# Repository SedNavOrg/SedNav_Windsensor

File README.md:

# SedNav_Windsensor

An open-source wind sensor design, taking inspiration from the project [Windsensor Yachta](https://github.com/norbert-walter/Windsensor_Yachta) by Norbert Walter.

It uses the same firmware, modified to work with this design.

The aims of this derivation are :

- To simplify the building process, by making the PCB easier to solder by hand

- To simplify the flashing, by using the ESP32C3 or C6 with a built-in USB interface (no more need for a serial to USB converter)

- To reduce the size of the wind sensor, by shrinking the pcb and reworking the design, in order to reduce the wind resistance, making it more resilient to winds.

- To test and validate the design in an actual wind tunnel.

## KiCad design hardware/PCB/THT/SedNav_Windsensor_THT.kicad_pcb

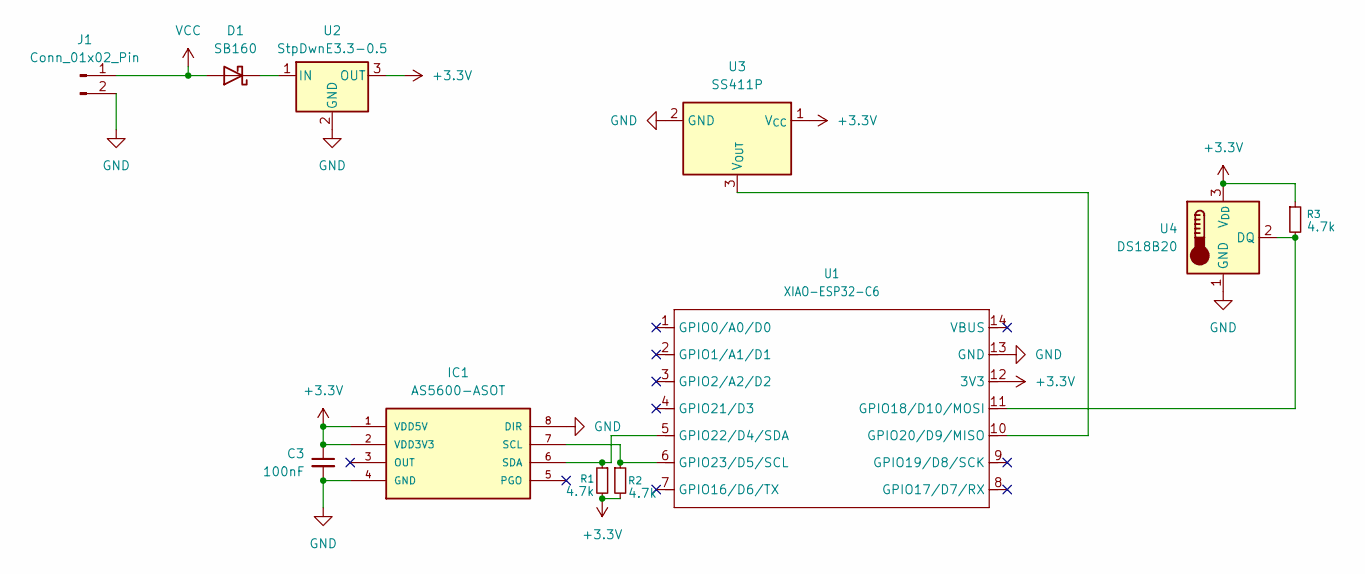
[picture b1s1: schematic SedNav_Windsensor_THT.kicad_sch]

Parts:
C3: 100nF; C_Disc_D4.7mm_W2.5mm_P5.00mm
D1: SB160; D_DO-41_SOD81_P7.62mm_Horizontal
IC1: AS5600-ASOT; SOIC127P600X175-8N; MOUSER_PART_NUMBER 985-AS5600-ASOT
J1: Conn_01x02_Pin; TerminalBlock_Phoenix_MPT-0,5-2-2.54_1x02_P2.54mm_Horizontal
R1, R2, R3: 4.7k; R_Axial_DIN0207_L6.3mm_D2.5mm_P7.62mm_Horizontal
U1: XIAO-ESP32-C6; XIAO-ESP32C6-THT
U2: StpDwnE3.3-0.5; CONV_R-78K3.3-0.5
U3: SS411P
U4: DS18B20; TO-92_Inline_Wide

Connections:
+3.3V: C3.1, IC1.1 (VDD5V), IC1.2 (VDD3V3), R1.2, R2.2, R3.1, U1.12 (3V3), U2.3 (OUT), U3.1 (V_{CC}), U4.3 (V_{DD})
GND: C3.2, IC1.4 (GND), IC1.8 (DIR), J1.2, U1.13 (GND), U2.2 (GND), U3.2 (GND), U4.1 (GND)
unnamed: D1.1 (K), U2.1 (IN)
unnamed: IC1.7 (SCL), R2.1, U1.6 (GPIO23/D5/SCL)
unnamed: IC1.6 (SDA), R1.1, U1.5 (GPIO22/D4/SDA)
unnamed: R3.2, U1.11 (GPIO18/D10/MOSI), U4.2 (DQ)
unnamed: U1.10 (GPIO20/D9/MISO), U3.3 (V_{OUT})
VCC: D1.2 (A), J1.1

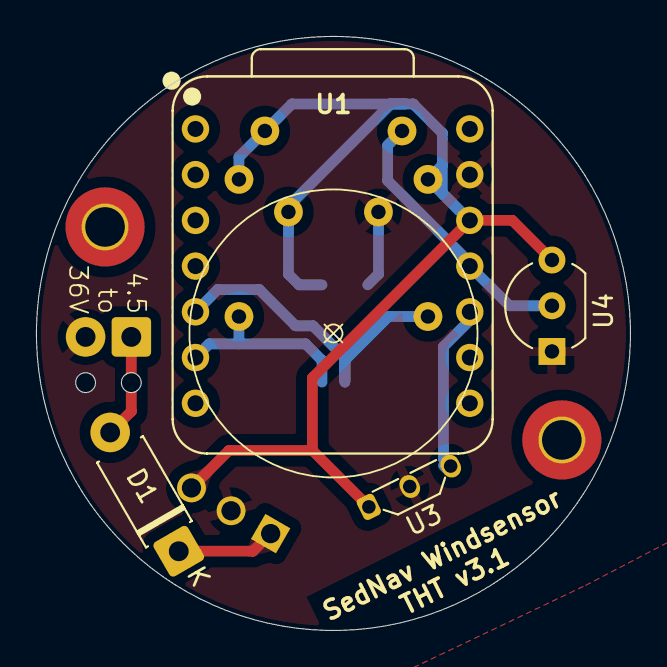
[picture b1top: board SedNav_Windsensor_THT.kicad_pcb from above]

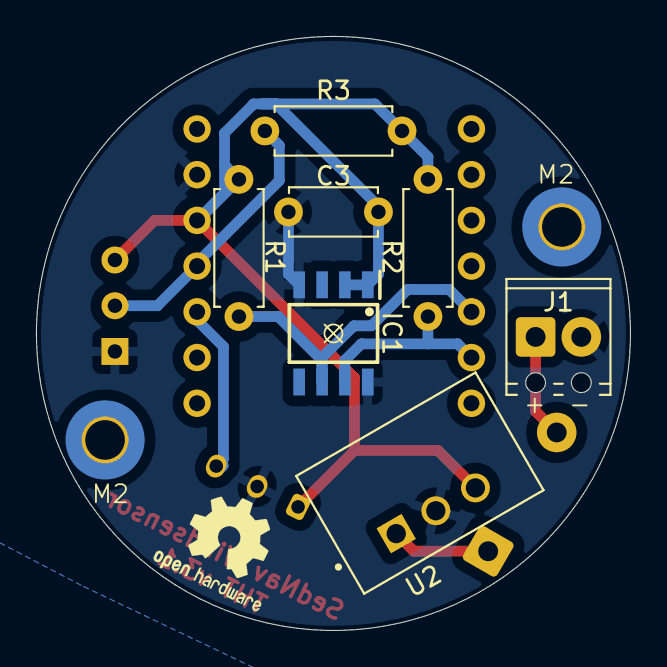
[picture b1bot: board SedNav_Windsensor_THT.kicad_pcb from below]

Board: 2 copper layers, 33.0 x 33.0 mm, 13 parts (9 on the bottom side), 8 nets.

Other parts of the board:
M2_1, M2_2: MountingHole_2.2mm_M2_Pad_TopBottom

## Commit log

2025-10-15 Corrected component sizes and added teardrops
2025-11-04 Modified PCB to match Simon's remarks Moved the esp32 to a side, to be able to access the usb port Simplified the routing Made the board more aesthetically pleasing
2025-11-15 Added software, corrected for ESP32C6 (untested)
2025-11-25 Firmware partialy operational. Need to correct the temperature, and verify the NMEA works.
2025-12-15 Corrected EEPROM initialization and saving function. Verified connecting to boat wifi works.
2025-12-16 Corrected temperature sensor bug
2025-12-17 Update README to reflect project name change and outline design aims
2025-12-19 Correction de la connexion avec hotspot non sécurisé
2025-12-21 v2 du PCB (en THT)
2026-01-22 Changed connector
2026-01-22 Version alpha d'une version SMD de la carte élec
2026-01-31 V3.1 du PCB THT
2026-01-31 Mise un jour d'un pin du firmware, et suppression du c3
2026-02-07 Version finale, fin du projet
2026-02-07 Ajout du lien vers la CAO OnShape
2026-02-07 Ajout des licences
2026-02-08 Ajout de la possibilité de faire un firmware merged
2026-02-09 Fix the merged firwmare script for espwebtools
2026-02-09 Corrected wind speed readings when no wind is present
2026-02-09 Mise à jour des valeurs par défaut pour le windsensor sednav
